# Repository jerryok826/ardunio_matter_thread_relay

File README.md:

# Matter-over-Thread 4-Channel Intelligent Relay Controller

The board shown below is an Arduino Matter/Thread relay controller designed for use with an Apple HomeKit network. It uses an Arduino Nano Matter processor to control four onboard relays, which can be used to operate motors, lights, valves, or other electrical loads.

Each relay can be controlled locally using the onboard pushbuttons, allowing users to manually enable or disable individual outputs. Through the Apple Home app on an iPhone, each relay can also be monitored and controlled remotely from anywhere with internet access.

An integrated OLED display provides system status information, including Thread network signal strength. During initial setup, the display presents a QR code that can be scanned to quickly add the device to the Apple Home app.

The board also includes an I²C Qwiic connector for attaching external sensors and peripherals. For example, a rain sensor could be connected to automatically disable irrigation valves during rainfall, helping conserve water and prevent overwatering.

**Status:** The board completely supports relay control. The I²C Qwiic connector is wired wrong. There are other physical placements that need updating. So the board will be turned. Gerber files will be punished after these changes.

An industrial-grade, ultra-low-latency 4-Channel Relay Controller built using the **Arduino Nano Matter** (Silicon Labs MGM240S core). This project connects natively with Apple Home, Home Assistant, and other Matter ecosystems over a self-healing Thread mesh network.

Featuring an asynchronous hardware override architecture, non-blocking FreeRTOS thread watchdogs, and an integrated I2C OLED display that acts as a standalone **RF Survey & Walk-Testing Tool**, this project is designed for robust, long-term smart home panel automation.

---

## ✨ Key Features

- **Ecosystem Unified Build:** Native Matter protocol integration that auto-populates as four independent, sequential switch endpoints in your smart home application.
- **Zero App Dependence Override:** Local manual buttons run entirely on edge-triggered **Asynchronous Hardware Interrupts**. Relays switch locally within microseconds even if your smart home hub is offline or entirely destroyed.
- **Anti-Race Watchdog:** Implements a non-blocking 50ms throttled execution pacing engine to prevent Matter application layer data collisions and loop freezing.
- **Failsafe Boot Protection:** Firmware forces relay pins to an explicit `LOW` state prior to opening output drivers. Combined with physical pull-down networks, this eliminates clicks or accidental appliance cycles during microcontroller reboots.
- **Dual-OLED Matrix Engine:** Dynamic runtime support for both **SH1106** and **SSD1306** I2C displays via a simple preprocessor toggle.
- **Standalone RF Survey Tool:** Displays a dynamic pairing QR code on boot, then transitions automatically into a real-time system dashboard mapping your Thread Node Role and precise signal attenuation metrics (`dBm`) on a fast 3-second cycle.

---

## 🛠️ Hardware Requirements & Pinout

### Core Microcontroller
- [Arduino Nano Matter](https://arduino.cc) (Silicon Labs MGM240S)

### Supported Displays
- 0.96" I2C OLED Display (**SH1106 Recommended** for native border alignment, or SSD1306)

### Physical Netlist Connection Map

| Arduino Pin | Hardware Component | Electrical Specification / Circuit Design |
| :--- | :--- | :--- |
| **D2** | Relay 1 Trigger Output | Active-HIGH Latch (Must use 10kΩ external Pull-Down to GND) |
| **D3** | Relay 2 Trigger Output | Active-HIGH Latch (Must use 10kΩ external Pull-Down to GND) |
| **D4** | Relay 3 Trigger Output | Active-HIGH Latch (Must use 10kΩ external Pull-Down to GND) |
| **D5** | Relay 4 Trigger Output | Active-HIGH Latch (Must use 10kΩ external Pull-Down to GND) |
| **D6** | Manual Button 1 Input | Short-to-GND Momentary Switch (Relies on internal `INPUT_PULLUP`) |
| **D7** | Manual Button 2 Input | Short-to-GND Momentary Switch (Relies on internal `INPUT_PULLUP`) |
| **D8** | Manual Button 3 Input | Short-to-GND Momentary Switch (Relies on internal `INPUT_PULLUP`) |
| **D9** | Manual Button 4 Input | Short-to-GND Momentary Switch (Relies on internal `INPUT_PULLUP`) |
| **A4 / SDA**| OLED Serial Data Line | I2C Data (Include physical 4.7kΩ external Pull-Up to 3.3V) |
| **A5 / SCL**| OLED Serial Clock Line | I2C Clock (Include physical 4.7kΩ external Pull-Up to 3.3V) |
| **BTN_BUILTIN**| Factory Reset Trigger | Physical button on Nano Matter. Hold 10s to wipe Matter Fabric. |

> ⚠️ **CRITICAL DEVELOPER WARNING:** The Arduino Nano Matter GPIO pins safely output a maximum of **4mA to 8mA**. Standard mechanical relay coils draw between **70mA and 100mA**. **Do not wire relay coils directly to the Arduino pins.** You must use transistor switches (e.g., 2N2222) or optocouplers (e.g., PC817) on your custom PCB to isolate the driver currents.

---

## 💻 Firmware Installation & Configuration

### 1. Prerequisites
Ensure your Arduino IDE environment is properly updated:
1. Open the Arduino IDE, go to **Tools > Board > Boards Manager** and install the **Arduino Nano Matter** board package.
2. Go to **Tools > Manage Libraries** and install these exact dependencies:
   - `SSD1306Ascii` (by Bill Greiman)
   - `QRCode` (by Richard Moore)

### 2. IDE Compilation Configuration
Before flashing the firmware, you **must** configure the low-level stack settings:
- Go to **Tools > Protocol Stack** and select **Matter**. 
- *Note: If this is left on "None", the compiler will completely ignore all Matter initialization sequences.*

### 3. Display Selection Toggle
At the very top of the primary sketch file, uncomment the specific preprocessor definition that matches your physical OLED module hardware:

```cpp
// UNCOMMENT ONLY ONE of the options below to match your physical OLED panel:
#define DISPLAY_TYPE_SH1106      // Use this if your screen has an SH1106 controller
// #define DISPLAY_TYPE_SSD1306  // Use this if your screen has a true SSD1306 controller
```

---

## 📱 Provisioning & First-Time Setup

1. Flash the firmware to your board and open your serial monitor at **115200 baud**.
2. Upon boot, the board will automatically check its secure enclave storage rows. If it is uncommissioned, a custom **Version 3 QR Matrix** will automatically render on the left side of your OLED screen.
3. Open your native smart home app (e.g., **Apple Home**) on your iPhone.
4. Tap **Add Accessory** and point your camera at the OLED glass panel.
5. **Alternative Manual Flow:** If the camera cannot capture the display grid due to enclosure glare, tap *More Options / I Don't Have a Code*, select the module from the nearby Bluetooth list, and manually input the static 11-digit setup passcode:
   ```text
   Manual Setup Code: 3497-0259-332
   ```
6. Keep your phone close to the hardware for the first 30 seconds. The initial handshake executes over Bluetooth Low Energy (BLE) before moving the board permanently to your home's **Thread Mesh Network**.

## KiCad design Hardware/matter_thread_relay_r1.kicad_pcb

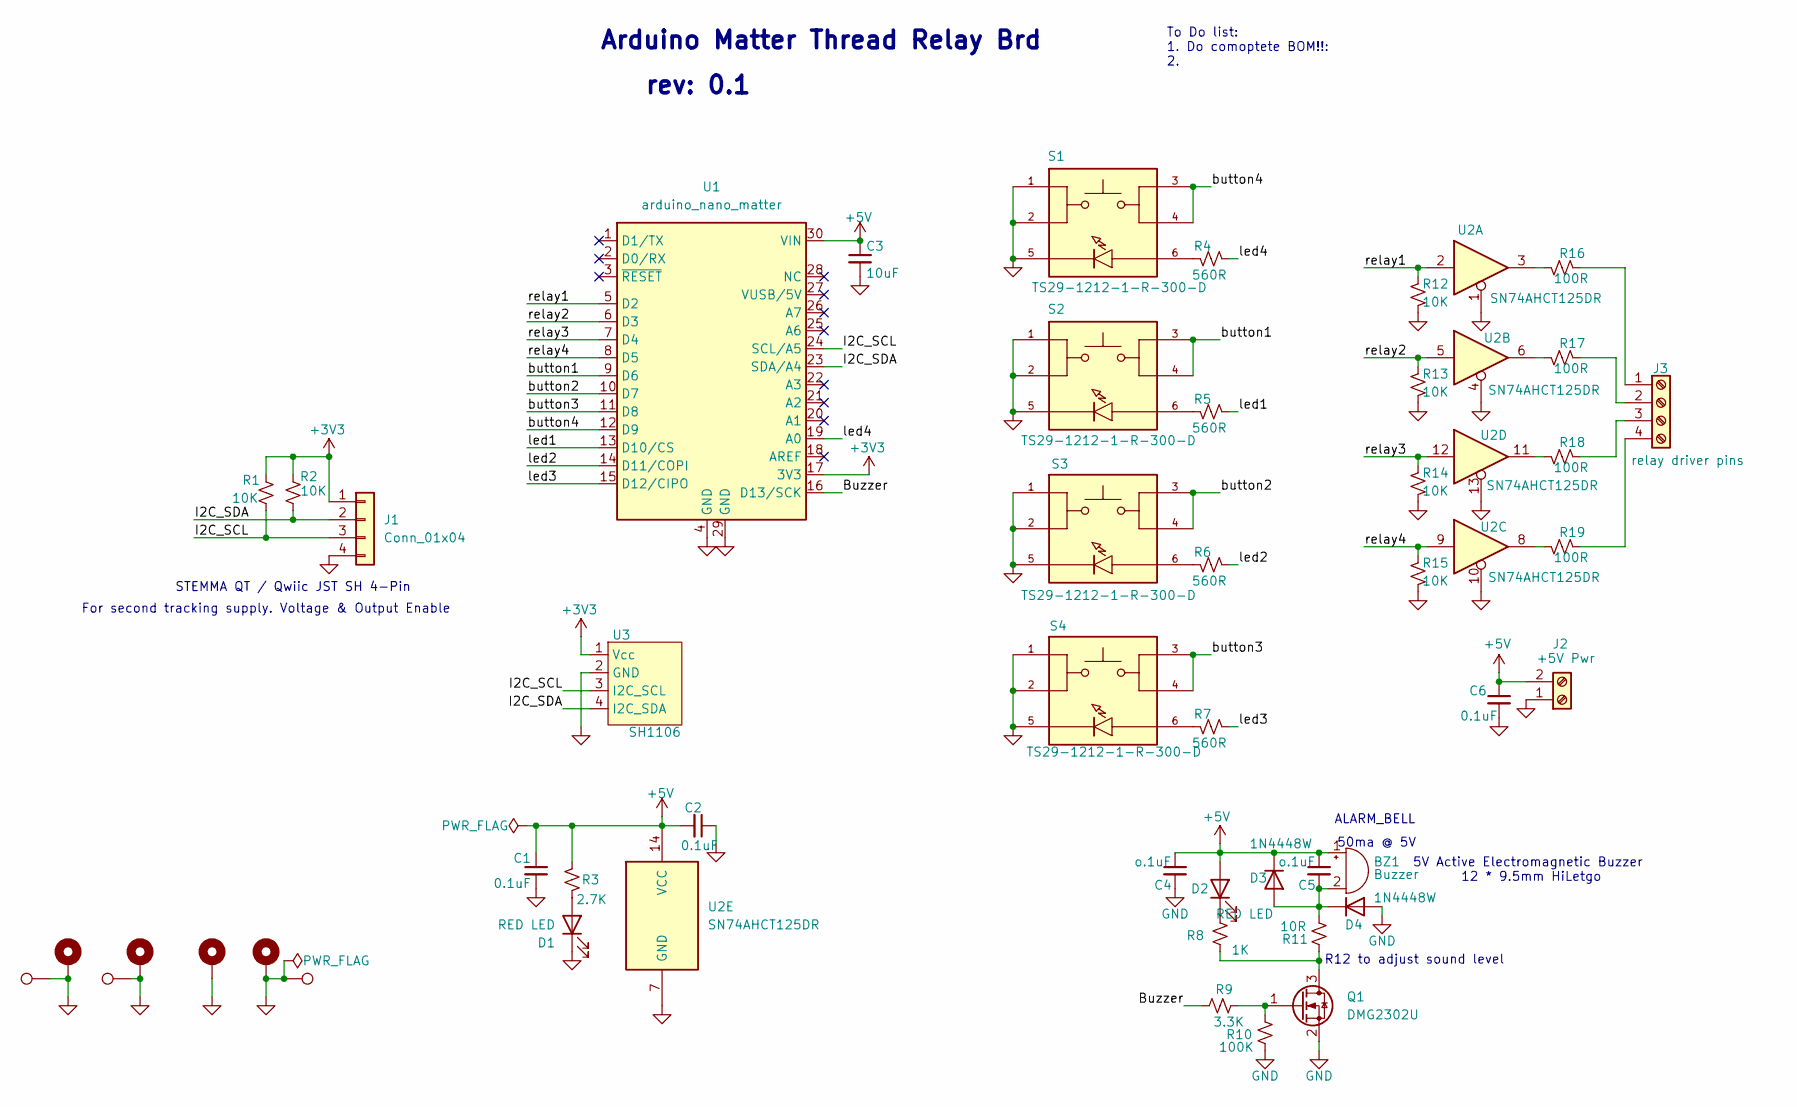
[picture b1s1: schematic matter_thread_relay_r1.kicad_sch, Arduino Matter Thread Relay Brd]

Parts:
BZ1: Buzzer; Buzzer_12x9.5RM7.6
C1, C2, C6: 0.1uF; C_0805_2012Metric_Pad1.18x1.45mm_HandSolder
C3: 10uF; C_0805_2012Metric_Pad1.18x1.45mm_HandSolder
C4, C5: o.1uF; C_0805_2012Metric_Pad1.18x1.45mm_HandSolder
D1, D2: RED LED; LED_1206_3216Metric_Pad1.42x1.75mm_HandSolder
D3, D4: 1N4448W; D_SOD-123
GND1, GND2, GND3: GND; TestPoint_THTPad_D2.0mm_Drill1.0mm
H1, H2, H4, H6: MountingHole_Pad; MountingHole_3.2mm_M3_ISO7380_Pad_TopBottom
J1: Conn_01x04; JST_SH_SM04B-SRSS-TB_1x04-1MP_P1.00mm_Horizontal
J2: +5V Pwr; TerminalBlock_CUI_TB007-508-02_1x02_P5.08mm_Horizontal
J3: relay driver pins; TerminalBlock_CUI_TB007-508-04_1x04_P5.08mm_Horizontal
Q1: DMG2302U; SOT-23
R1, R2, R12, R13, R14, R15: 10K; R_0805_2012Metric_Pad1.20x1.40mm_HandSolder
R3: 2.7K; R_0805_2012Metric_Pad1.20x1.40mm_HandSolder
R4, R5, R6, R7: 560R; R_0805_2012Metric_Pad1.20x1.40mm_HandSolder
R8: 1K; R_0805_2012Metric_Pad1.20x1.40mm_HandSolder
R9: 3.3K; R_0805_2012Metric_Pad1.20x1.40mm_HandSolder
R10: 100K; R_0805_2012Metric_Pad1.20x1.40mm_HandSolder
R11: 10R; R_0805_2012Metric_Pad1.20x1.40mm_HandSolder
R16, R17, R18, R19: 100R; R_0805_2012Metric_Pad1.20x1.40mm_HandSolder
S1, S2, S3, S4: TS29-1212-1-R-300-D; SW_TS29-1212-1-R-300-D; PARTREV 1.01
U1: arduino_nano_matter; Arduino_Nano
U2: SN74AHCT125DR; SO-14_5.3x10.2mm_P1.27mm
U3: SH1106

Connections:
+3V3: J1.1, R1.2, R2.2, U1.17 (3V3), U3.1 (Vcc)
+5V: BZ1.1 (+), C1.1, C2.2, C3.1, C4.1, C5.1, C6.1, D2.2 (A), D3.1 (K), J2.2, R3.2, U1.30 (VIN), U2.14 (VCC)
/Buzzer: R9.2, U1.16 (D13/SCK)
/I2C_SCL: J1.3, R1.1, U1.24 (SCL/A5), U3.3 (I2C_SCL)
/I2C_SDA: J1.2, R2.1, U1.23 (SDA/A4), U3.4 (I2C_SDA)
/button1: S2.3, S2.4, U1.9 (D6)
/button2: S3.3, S3.4, U1.10 (D7)
/button3: S4.3, S4.4, U1.11 (D8)
/button4: S1.3, S1.4, U1.12 (D9)
/led1: R5.1, U1.13 (D10/CS)
/led2: R6.1, U1.14 (D11/COPI)
/led3: R7.1, U1.15 (D12/CIPO)
/led4: R4.1, U1.19 (A0)
/relay1: R12.2, U1.5 (D2), U2.2
/relay2: R13.2, U1.6 (D3), U2.5
/relay3: R14.2, U1.7 (D4), U2.12
/relay4: R15.2, U1.8 (D5), U2.9
GND: C1.2, C2.1, C3.2, C4.2, C6.2, D1.1 (K), D4.2 (A), GND1.1, GND2.1, GND3.1, H1.1, H2.1, H4.1, H6.1, J1.4, J2.1, Q1.2 (S), R10.2, R12.1, R13.1, R14.1, R15.1, S1.1, S1.2, S1.5, S2.1, S2.2, S2.5, S3.1, S3.2, S3.5, S4.1, S4.2, S4.5, U1.4 (GND), U1.29 (GND), U2.1, U2.4, U2.7 (GND), U2.10, U2.13, U3.2 (GND)
unnamed: BZ1.2 (-), C5.2, D3.2 (A), D4.1 (K), R11.1
unnamed: D1.2 (A), R3.1
unnamed: D2.1 (K), R8.1
unnamed: J3.1, R16.1
unnamed: J3.2, R17.1
unnamed: J3.3, R18.1
unnamed: J3.4, R19.1
unnamed: Q1.3 (D), R8.2, R11.2
unnamed: Q1.1 (G), R9.1, R10.1
unnamed: R4.2, S1.6
unnamed: R5.2, S2.6
unnamed: R6.2, S3.6
unnamed: R7.2, S4.6
unnamed: R16.2, U2.3
unnamed: R17.2, U2.6
unnamed: R18.2, U2.11
unnamed: R19.2, U2.8

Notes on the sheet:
To Do list: 1. Do comoptete BOM!!: 2.
rev: 0.1
For second tracking supply. Voltage & Output Enable
5V Active Electromagnetic Buzzer 12 * 9.5mm HiLetgo
Arduino Matter Thread Relay Brd
ALARM_BELL
STEMMA QT / Qwiic JST SH 4-Pin
R12 to adjust sound level
50ma @ 5V

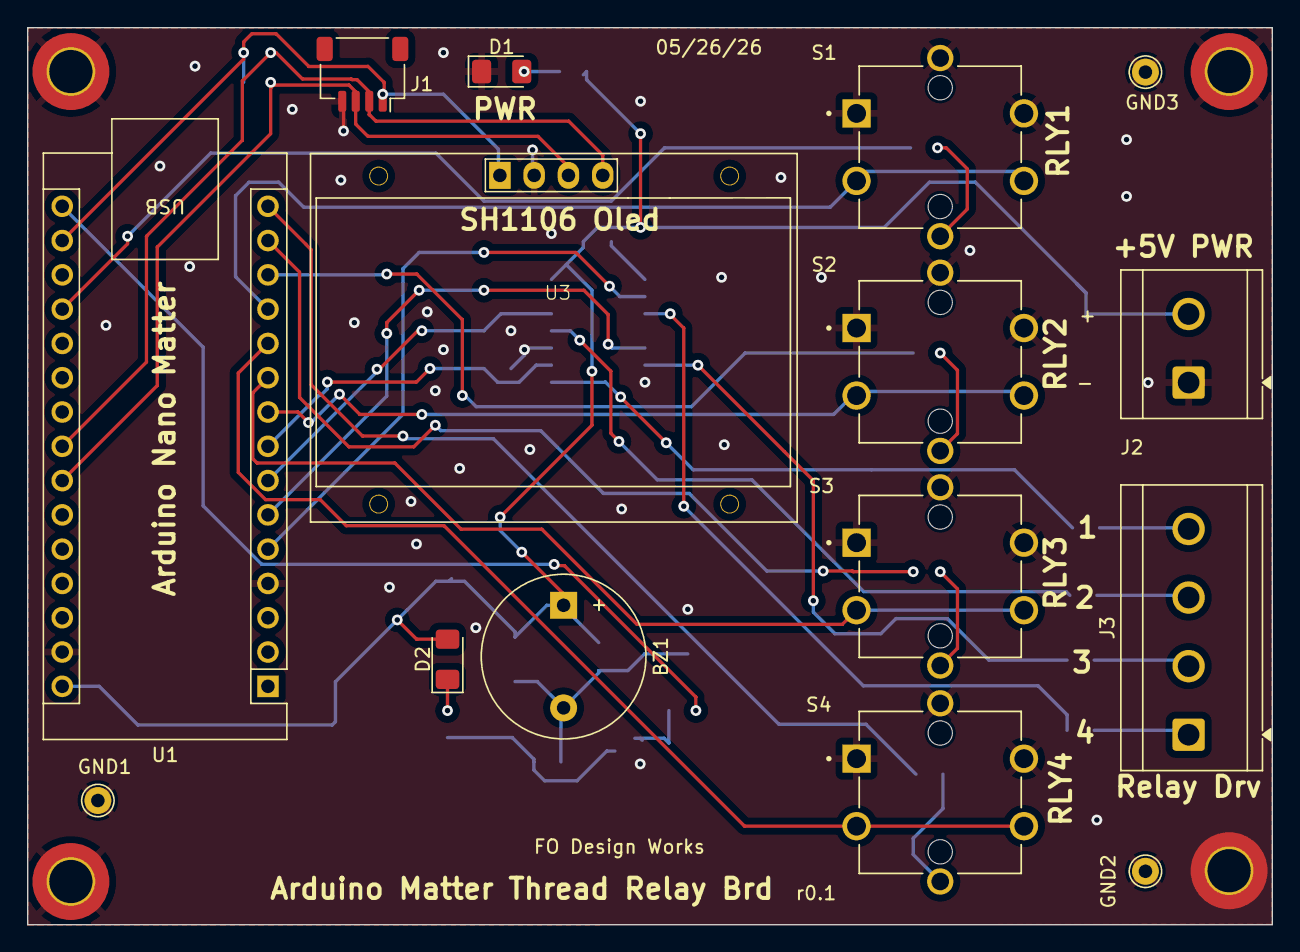
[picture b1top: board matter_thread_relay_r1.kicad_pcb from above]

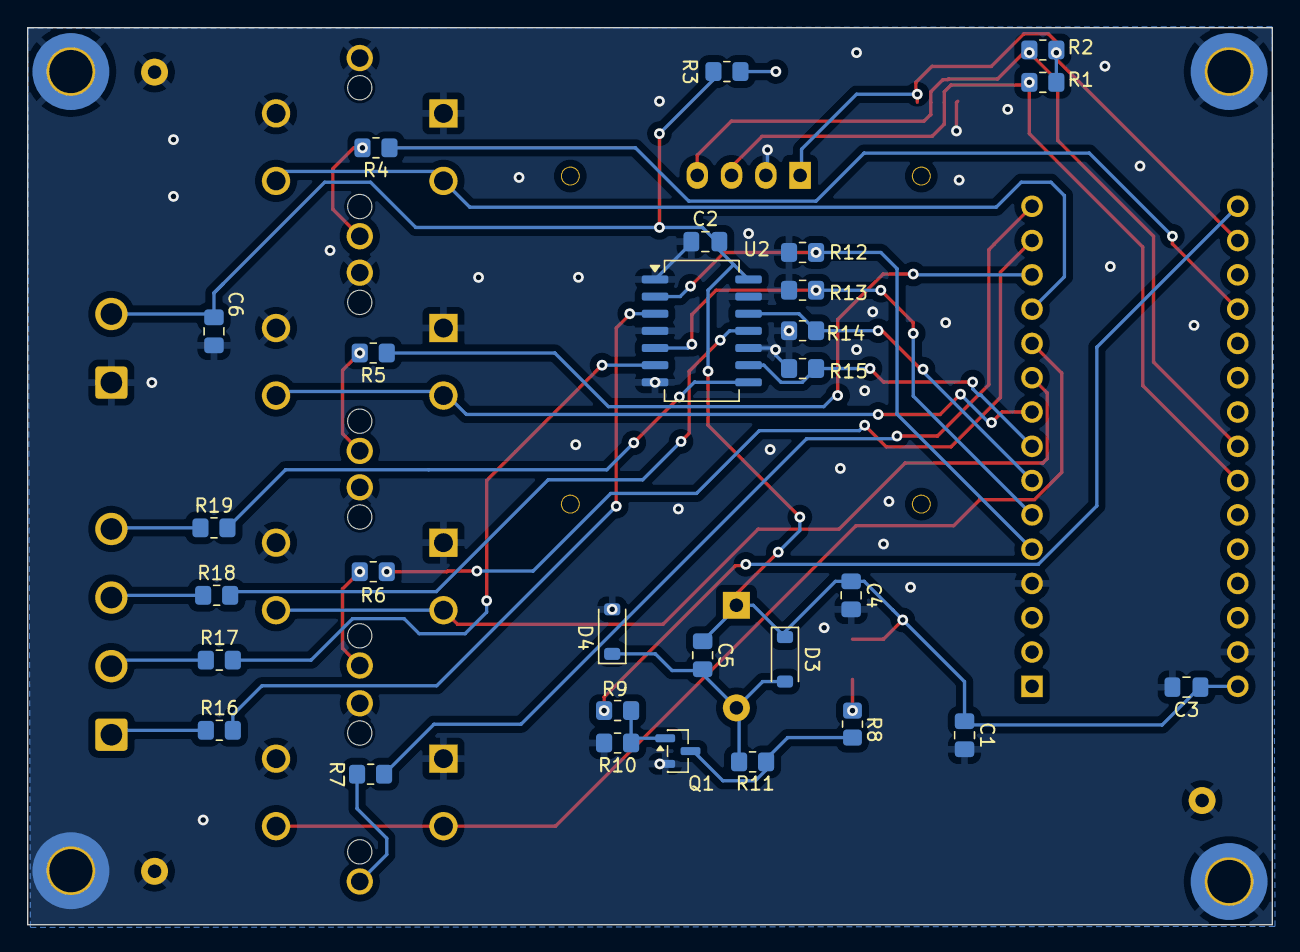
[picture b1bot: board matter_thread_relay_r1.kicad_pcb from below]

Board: 2 copper layers, 92.2 x 66.4 mm, 48 parts (29 on the bottom side), 35 nets.
